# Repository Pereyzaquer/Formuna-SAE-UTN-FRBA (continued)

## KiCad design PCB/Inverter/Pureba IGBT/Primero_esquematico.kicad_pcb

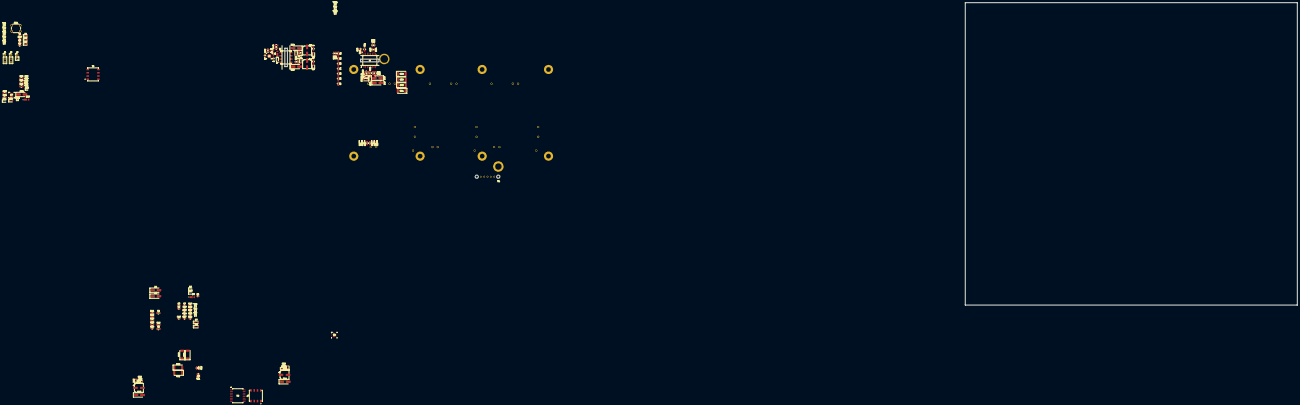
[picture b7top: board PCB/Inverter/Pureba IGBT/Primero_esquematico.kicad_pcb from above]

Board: 4 copper layers, 149 parts (1 on the bottom side), 78 nets.

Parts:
C1: 100pF; R_0603_1608Metric_Pad0.98x0.95mm_HandSolder
C2, C4, C17, C19, C32, C34, C35: 10uF; C_0805_2012Metric_Pad1.18x1.45mm_HandSolder
C3, C7, C13, C18, C22, C28: 100pF; C_0603_1608Metric_Pad1.08x0.95mm_HandSolder
C5, C20: 10pF; C_0603_1608Metric_Pad1.08x0.95mm_HandSolder
C6, C21: 47nF; C_0603_1608Metric_Pad1.08x0.95mm_HandSolder
C8, C9, C23, C24: 100nF; C_0603_1608Metric_Pad1.08x0.95mm_HandSolder
C10, C25: 220nF; C_0603_1608Metric_Pad1.08x0.95mm_HandSolder
C11, C12, C26, C27: 2.2uF; C_0805_2012Metric_Pad1.18x1.45mm_HandSolder
C14, C15, C29, C30: 22uF; CP_Elec_6.3x5.8
C16, C31: 1uF; C_0805_2012Metric_Pad1.18x1.45mm_HandSolder
C33: 47nF; R_0201_0603Metric_Pad0.64x0.40mm_HandSolder
D1, D2, D3, D15, D16, D28, D29, D34: APT2012EC; LED_0805_2012Metric_Pad1.15x1.40mm_HandSolder
D4, D5, D17, D18: STTH112A; D_SMA_Handsoldering
D6, D19: BAT54WS-7-F; D_SOD-323F
D7, D20: BZT52C2V7-TP; Nexperia_CFP3_SOD-123W
D8, D21: MMSZ5242B-7-F; Nexperia_CFP3_SOD-123W
D9, D22, D30: DFLZ24Q-7; DIO_DFLS130L-7
D10, D23, D31: 1N4148WS-Q; D_SOD-323F
D11, D12, D24, D25, D32: VS-10MQ100NTRPBF; D_SMA_Handsoldering
D13, D26: BZT52-B8V2_R1_00001; Nexperia_CFP3_SOD-123W
D14, D27: BZT52C18-7-F; Nexperia_CFP3_SOD-123W
D33: SZMM5Z5V6T1G; D_SOD-523
J1, J2: Molex 3; PinHeader_1x03_P2.54mm_Vertical
J3: Molex; PinHeader_1x02_P2.54mm_Vertical
R1, R28, R47: 6k8; R_0805_2012Metric_Pad1.20x1.40mm_HandSolder
R2, R3, R4, R5, R6, R7: 180k; R_0805_2012Metric_Pad1.20x1.40mm_HandSolder
R8, R9: 5k; R_0603_1608Metric_Pad0.98x0.95mm_HandSolder
R10: 15k; R_0603_1608Metric_Pad0.98x0.95mm_HandSolder
R11, R30: 590; R_0805_2012Metric_Pad1.20x1.40mm_HandSolder
R12, R31: 475; R_0805_2012Metric_Pad1.20x1.40mm_HandSolder
R13, R32: 307k; C_0603_1608Metric_Pad1.08x0.95mm_HandSolder
R14, R33: 37k; C_0603_1608Metric_Pad1.08x0.95mm_HandSolder
R15, R16, R34, R35: 2k; R_0805_2012Metric_Pad1.20x1.40mm_HandSolder
R17, R36: 12k1; C_0603_1608Metric_Pad1.08x0.95mm_HandSolder
R18, R37: 200k; C_0603_1608Metric_Pad1.08x0.95mm_HandSolder
R19, R20, R38, R39: 4.7; D_2512_6332Metric_Pad1.52x3.35mm_HandSolder
R21, R22, R40, R41: 10; D_2512_6332Metric_Pad1.52x3.35mm_HandSolder
R23, R42: 10; C_0603_1608Metric_Pad1.08x0.95mm_HandSolder
R24, R43: 154k; C_0603_1608Metric_Pad1.08x0.95mm_HandSolder
R25, R26, R44, R45: 100; C_0603_1608Metric_Pad1.08x0.95mm_HandSolder
R27, R46: 360; C_0603_1608Metric_Pad1.08x0.95mm_HandSolder
R29, R48: 15k; R_0805_2012Metric_Pad1.20x1.40mm_HandSolder
R49: 307k; R_0201_0603Metric_Pad0.64x0.40mm_HandSolder
R50: 37k; R_0201_0603Metric_Pad0.64x0.40mm_HandSolder
R51: 12k; R_0201_0603Metric_Pad0.64x0.40mm_HandSolder
R52: 73k2; R_0201_0603Metric_Pad0.64x0.40mm_HandSolder
R53: 110k; R_0805_2012Metric_Pad1.20x1.40mm_HandSolder
R54: 1k5; R_0805_2012Metric_Pad1.20x1.40mm_HandSolder
SW1: SW_Push; SW_PUSH_6mm
T1, T2: 750317595; WE-FLYTI_EP7_4436
T3: 750317605; WE-FLYTI_EP7_4436
TP1, TP2, TP3, TP4, TP5: TP; TestPoint_Pad_1.0x1.0mm
TP6, TP7, TP8, TP9, TP10, TP11, TP12: TestPoint; TestPoint_Pad_1.0x1.0mm
U1: HAH3DR 800-S07SP4
U2: FS950R08A6P2BBPSA1; IC_FS950R08A6P2BBPSA1
U3, U5, U7: LM25180QNGURQ1; NGU0008C
U4, U6: UCC21750QDWRQ1; SOIC16_DW_TEX-M

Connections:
+3.3V: C16.2, C31.2, C34.2, C35.2, D32.1 (K), D33.1 (K), R8.1, R9.1, R10.2, R54.1, TP12.1, U4.15 (VCC), U6.15 (VCC)
+15V: C2.2, C4.2, C17.2, C19.2, C32.2, D9.2 (A), D22.2 (A), D30.2 (A), J3.1, R13.1, R32.1, R49.1, T1.4, T2.4, T3.4, U3.3 (VIN), U5.3 (VIN), U7.3 (VIN)
/Gate_Driver/*FLT: D1.2 (A), R8.2, U4.13 (*FLT), U6.13 (*FLT)
/Gate_Driver/C1_In_neg: C7.2, C28.2, J1.2, R25.1, R45.2, TP1.1
/Gate_Driver/C1_In_pos: C13.2, C22.2, J1.3, R26.2, R44.1, TP2.1
/Gate_Driver/Colec_2: D17.1 (K), R7.2, U2.C2
/Gate_Driver/G1: R19.1, R20.1, R21.1, R22.2, U2.G1, U4.7 (CLMPI)
/Gate_Driver/G2: R38.1, R39.1, R40.1, R41.2, U2.G2, U6.7 (CLMPI)
/Gate_Driver/GDsupply5/+15V: C24.2, C27.2, C30.1, D24.1 (K), D27.1 (K), R48.1, TP11.1, U6.5 (VDD)
/Gate_Driver/GDsupply5/-8V: C23.1, C26.1, C29.2, D25.2 (A), D26.2 (A), D28.1 (K), TP9.1, U6.8 (VEE)
/Gate_Driver/GDsupply5/DESAT: C18.2, D19.1 (K), D21.1 (K), R30.2, R31.1, U6.2 (DESAT)
/Gate_Driver/GDsupply5/S_HV: C20.1, R1.2, R2.1, R42.1
/Gate_Driver/GDsupply/+15V: C9.2, C12.2, C15.1, D11.1 (K), D14.1 (K), R29.1, TP8.1, U4.5 (VDD)
/Gate_Driver/GDsupply/-8V: C8.1, C11.1, C14.2, D12.2 (A), D13.2 (A), D15.1 (K), TP6.1, U4.8 (VEE)
/Gate_Driver/GDsupply/DESAT: C3.2, D6.1 (K), D8.1 (K), R11.2, R12.1, U4.2 (DESAT)
/Gate_Driver/ISO_GND: C3.1, C5.2, C8.2, C9.1, C11.2, C12.1, C14.1, C15.2, D6.2 (A), D8.2 (A), D13.1 (K), D14.2 (A), D16.1 (K), R11.1, R28.1, T1.6, T1.7, TP7.1, U2.T1, U4.3 (COM)
/Gate_Driver/ISO_GND_2: C18.1, C20.2, C23.2, C24.1, C26.2, C27.1, C29.1, C30.2, D19.2 (A), D21.2 (A), D26.1 (K), D27.2 (A), D29.1 (K), R1.1, R30.1, R47.1, T2.6, T2.7, TP10.1, U6.3 (COM)
/Gate_Driver/RDY: D2.2 (A), R9.2, U4.12 (RDY), U6.12 (RDY)
/Gate_Driver/Reset: C1.2, D3.2 (A), R10.1, SW1.2, U4.14 (RST/EN), U6.14 (RST/EN)
/Gate_Driver/S_TEMP: C5.1, R23.1, U2.T2
/Gate_Driver/Temp1: C10.1, J2.2, R27.1, TP3.1
/Gate_Driver/VCC_DC: D4.1 (K), U2.C1
/Gate_Driver/V_MP1: C25.1, J2.3, R46.1, TP4.1
GND: C1.1, C2.1, C4.1, C6.1, C7.1, C10.2, C13.1, C16.1, C17.1, C19.1, C21.1, C22.1, C25.2, C28.1, C31.1, C32.1, C33.1, C34.1, C35.1, D1.1 (K), D2.1 (K), D3.1 (K), D33.2 (A), D34.1 (K), J1.1, J2.1, J3.2, R14.2, R17.2, R33.2, R36.2, R50.2, R51.2, SW1.1, T3.5, T3.6, TP5.1, U3.8 (GND), U3.9 (PAD), U4.9 (GND), U5.8 (GND), U5.9 (PAD), U6.9 (GND), U7.8 (GND), U7.9 (PAD)
unnamed: D4.2 (A), D5.1 (K)
unnamed: D5.2 (A), D7.2 (A), R15.1, R16.1
unnamed: D7.1 (K), R12.2
unnamed: D10.2 (A), R24.1, T1.1, U3.1 (SW)
unnamed: D9.1 (K), D10.1 (K)
unnamed: D11.2 (A), T1.5
unnamed: D12.1 (K), T1.8
unnamed: D15.2 (A), R28.2
unnamed: D16.2 (A), R29.2
unnamed: D17.2 (A), D18.1 (K)
unnamed: D18.2 (A), D20.2 (A), R34.1, R35.1
unnamed: D20.1 (K), R31.2
unnamed: D22.1 (K), D23.1 (K)
unnamed: D23.2 (A), R43.1, T2.1, U5.1 (SW)
unnamed: D24.2 (A), T2.5
unnamed: D25.1 (K), T2.8
unnamed: D28.2 (A), R47.2
unnamed: D29.2 (A), R48.2
unnamed: D30.1 (K), D31.1 (K)
unnamed: D31.2 (A), R53.1, T3.1, U7.1 (SW)
unnamed: D32.2 (A), T3.7, T3.8
unnamed: D34.2 (A), R54.2
unnamed: R2.2, R3.1
unnamed: R3.2, R4.1
unnamed: R4.2, R5.1
unnamed: R5.2, R6.1
unnamed: R6.2, R7.1
unnamed: R13.2, R14.1, U3.4 (EN_UVLO)
unnamed: R24.2, U3.2 (FB)
unnamed: R18.2, U3.7 (RSET)
unnamed: C6.2, U3.5 (SS_BIAS)
unnamed: R17.1, R18.1, U3.6 (TC)
unnamed: R23.2, U4.1 (AIN)
unnamed: R27.2, U4.16 (APWM)
unnamed: R26.1, U4.11 (IN)
unnamed: R25.2, U4.10 (IN+)
unnamed: R15.2, R16.2, R19.2, R20.2, U4.4 (OUTH)
unnamed: R21.2, R22.1, U4.6 (OUTL)
unnamed: R32.2, R33.1, U5.4 (EN_UVLO)
unnamed: R43.2, U5.2 (FB)
unnamed: R37.2, U5.7 (RSET)
unnamed: C21.2, U5.5 (SS_BIAS)
unnamed: R36.1, R37.1, U5.6 (TC)
unnamed: R42.2, U6.1 (AIN)
unnamed: R46.2, U6.16 (APWM)
unnamed: R45.1, U6.11 (IN)
unnamed: R44.2, U6.10 (IN+)
unnamed: R34.2, R35.2, R38.2, R39.2, U6.4 (OUTH)
unnamed: R40.2, R41.1, U6.6 (OUTL)
unnamed: R49.2, R50.1, U7.4 (EN_UVLO)
unnamed: R53.2, U7.2 (FB)
unnamed: R52.2, U7.7 (RSET)
unnamed: C33.2, U7.5 (SS_BIAS)
unnamed: R51.1, R52.1, U7.6 (TC)

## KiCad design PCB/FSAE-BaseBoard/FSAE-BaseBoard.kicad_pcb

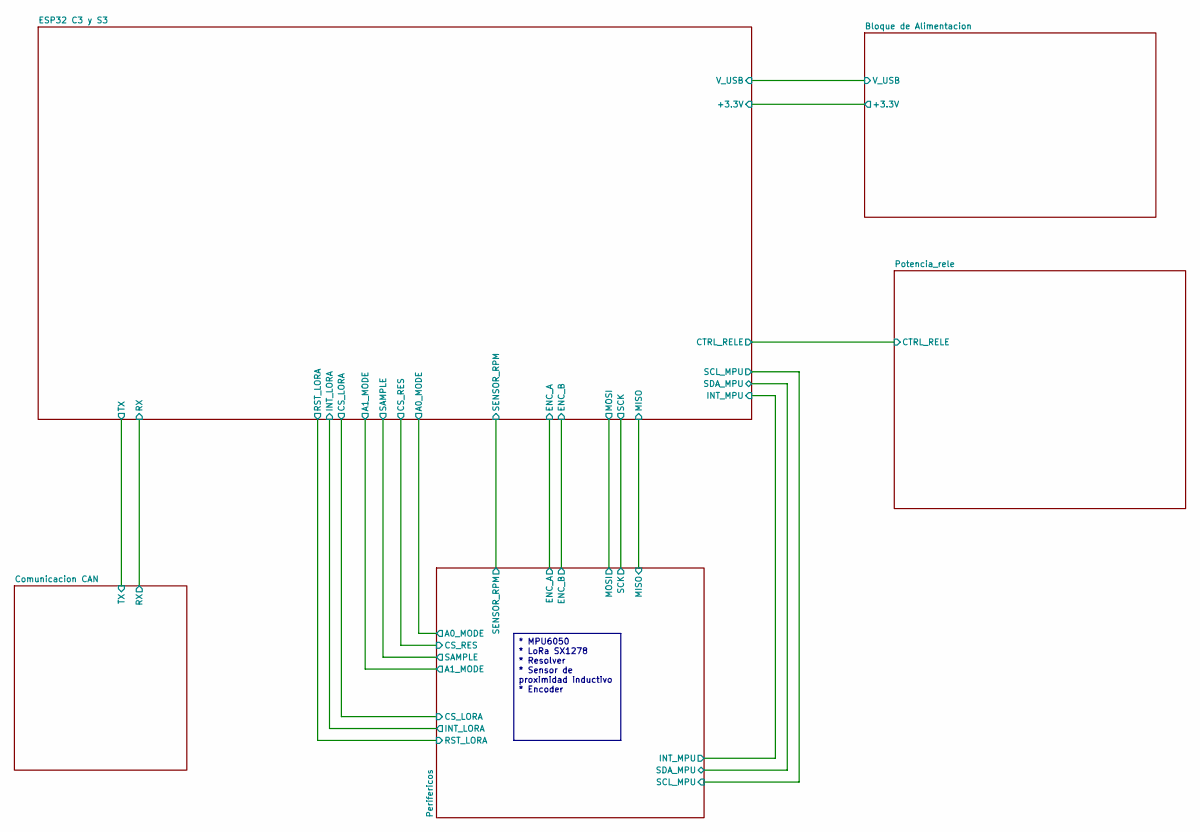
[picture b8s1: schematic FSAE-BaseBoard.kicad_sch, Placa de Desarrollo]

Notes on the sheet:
* MPU6050 * LoRa SX1278 * Resolver * Sensor de proximidad inductivo * Encoder

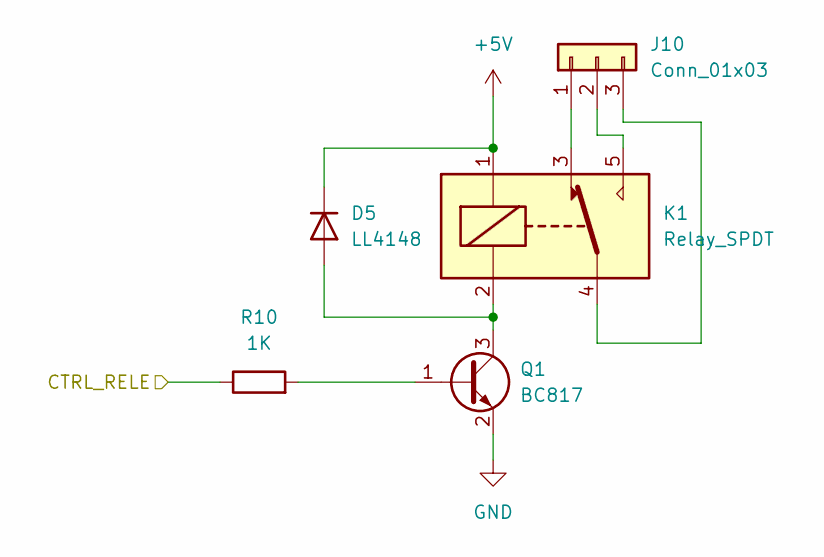
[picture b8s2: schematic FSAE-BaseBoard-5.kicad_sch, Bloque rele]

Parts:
D5: LL4148; D_MiniMELF
J10: Conn_01x03; PinHeader_1x03_P2.54mm_Vertical
K1: Relay_SPDT; Relay_SPDT_Omron-G5LE-1
Q1: BC817; SOT-23
R10: 1K; R_0805_2012Metric_Pad1.20x1.40mm_HandSolder

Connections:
+5V: D5.1 (K), K1.1; also elsewhere on the board
/ESP32 C3 y S3/CTRL_RELE: R10.1; also elsewhere on the board
GND: Q1.2 (E); also elsewhere on the board
unnamed: D5.2 (A), K1.2, Q1.3 (C)
unnamed: J10.1, K1.3
unnamed: J10.2, K1.5
unnamed: J10.3, K1.4
unnamed: Q1.1 (B), R10.2

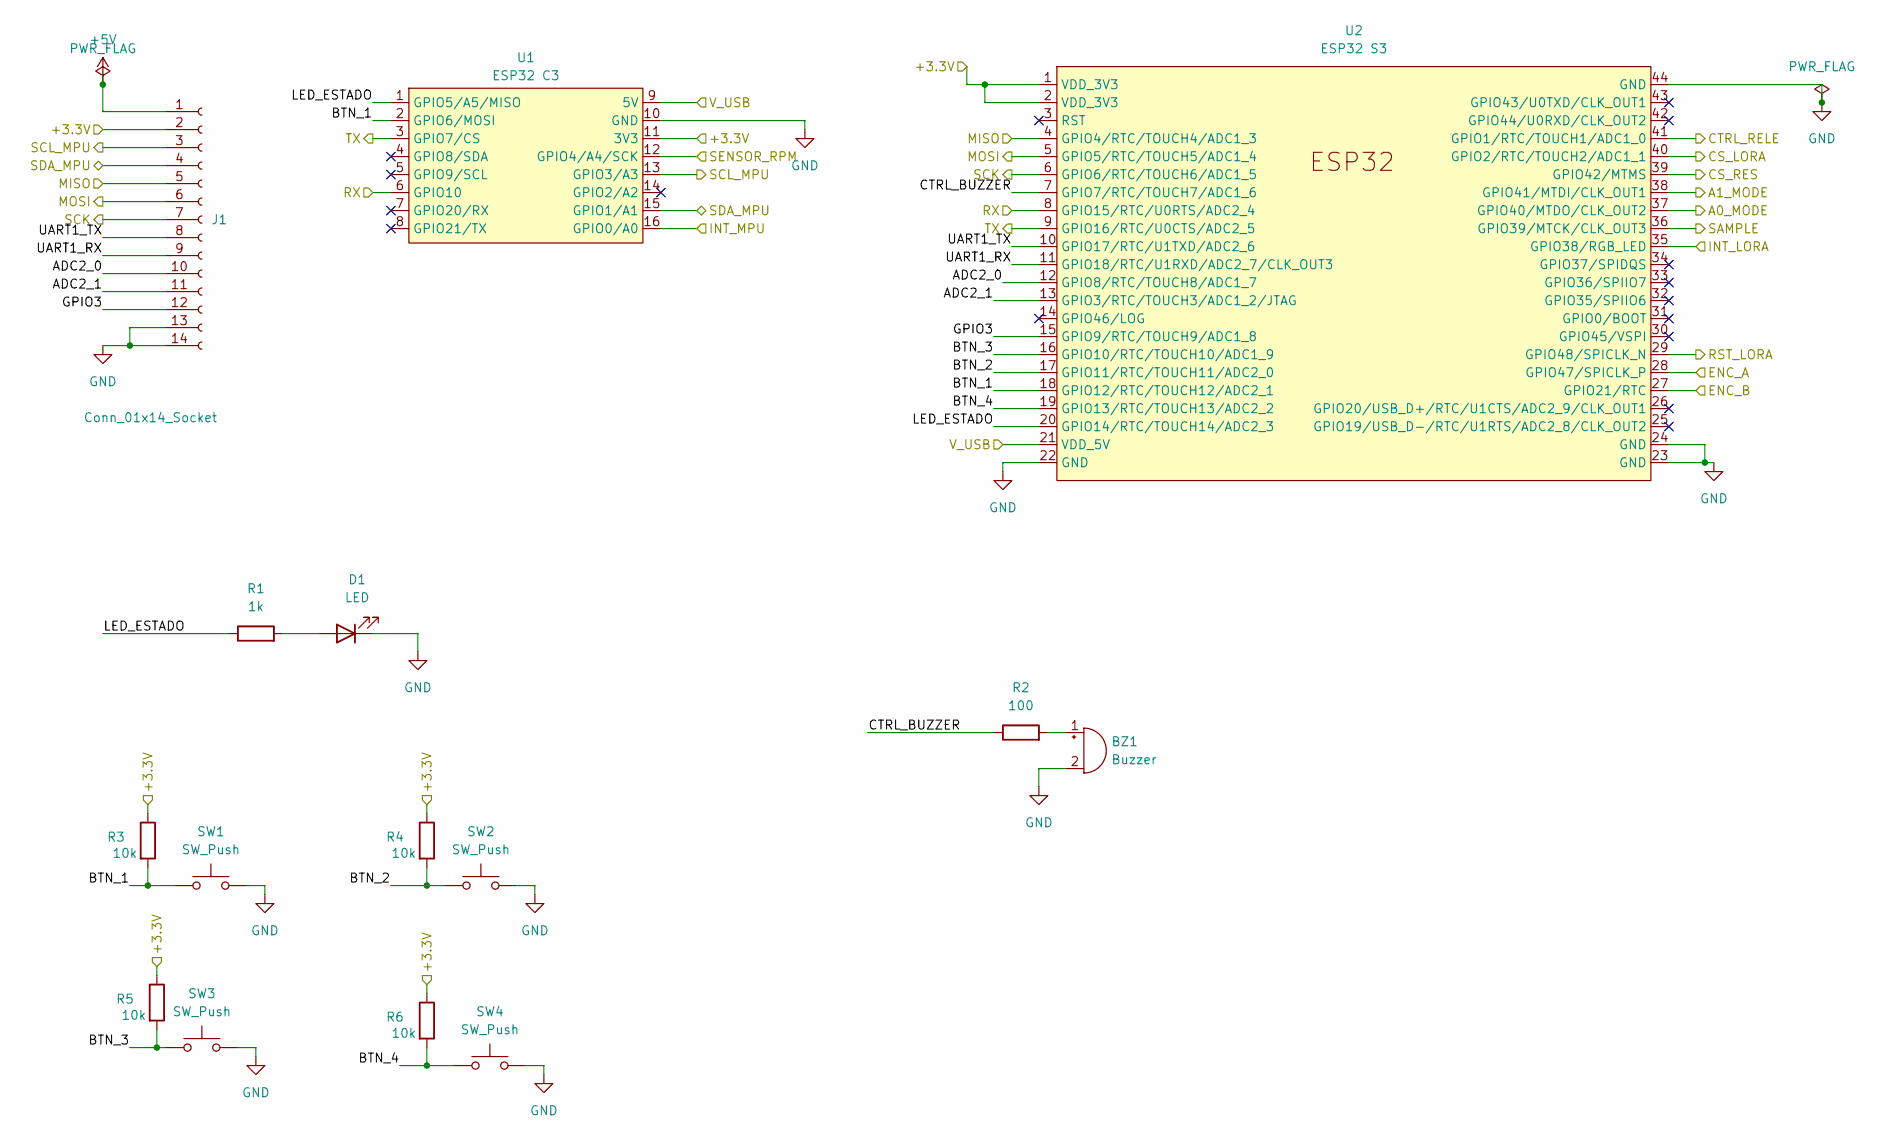
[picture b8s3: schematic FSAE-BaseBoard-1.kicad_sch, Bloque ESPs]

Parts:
BZ1: Buzzer; Buzzer_12x9.5RM7.6
D1: LED; LED_0805_2012Metric_Pad1.15x1.40mm_HandSolder
J1: Conn_01x14_Socket; PinSocket_1x14_P2.54mm_Vertical
R1: 1k; R_0805_2012Metric_Pad1.20x1.40mm_HandSolder
R2: 100; R_0805_2012Metric_Pad1.20x1.40mm_HandSolder
R3, R4, R5, R6: 10k; R_0805_2012Metric_Pad1.20x1.40mm_HandSolder
SW1, SW2, SW3, SW4: SW_Push; SW_PUSH_6mm_H5mm
U1: ESP32 C3; ESP32 C3 SM
U2: ESP32 S3

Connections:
+3.3V: J1.2, R3.1, R4.1, R5.1, R6.1, U1.11 (3V3), U2.1 (VDD_3V3), U2.2 (VDD_3V3); also elsewhere on the board
+5V: J1.1; also elsewhere on the board
/Bloque de Alimentacion/V_USB: U1.9 (5V), U2.21 (VDD_5V); also elsewhere on the board
/Comunicacion CAN/RX: U1.6 (GPIO10), U2.8 (GPIO15/RTC/U0RTS/ADC2_4); also elsewhere on the board
/Comunicacion CAN/TX: U1.3 (GPIO7/CS), U2.9 (GPIO16/RTC/U0CTS/ADC2_5); also elsewhere on the board
/ESP32 C3 y S3/A0_MODE: U2.37 (GPIO40/MTDO/CLK_OUT2); also elsewhere on the board
/ESP32 C3 y S3/A1_MODE: U2.38 (GPIO41/MTDI/CLK_OUT1); also elsewhere on the board
/ESP32 C3 y S3/ADC2_0: J1.10, U2.12 (GPIO8/RTC/TOUCH8/ADC1_7)
/ESP32 C3 y S3/ADC2_1: J1.11, U2.13 (GPIO3/RTC/TOUCH3/ADC1_2/JTAG)
/ESP32 C3 y S3/BTN_1: R3.2, SW1.1, U1.2 (GPIO6/MOSI), U2.18 (GPIO12/RTC/TOUCH12/ADC2_1)
/ESP32 C3 y S3/BTN_2: R4.2, SW2.1, U2.17 (GPIO11/RTC/TOUCH11/ADC2_0)
/ESP32 C3 y S3/BTN_3: R5.2, SW3.1, U2.16 (GPIO10/RTC/TOUCH10/ADC1_9)
/ESP32 C3 y S3/BTN_4: R6.2, SW4.1, U2.19 (GPIO13/RTC/TOUCH13/ADC2_2)
/ESP32 C3 y S3/CS_LORA: U2.40 (GPIO2/RTC/TOUCH2/ADC1_1); also elsewhere on the board
/ESP32 C3 y S3/CS_RES: U2.39 (GPIO42/MTMS); also elsewhere on the board
/ESP32 C3 y S3/CTRL_BUZZER: R2.1, U2.7 (GPIO7/RTC/TOUCH7/ADC1_6)
/ESP32 C3 y S3/CTRL_RELE: U2.41 (GPIO1/RTC/TOUCH1/ADC1_0); also elsewhere on the board
/ESP32 C3 y S3/ENC_A: U2.28 (GPIO47/SPICLK_P); also elsewhere on the board
/ESP32 C3 y S3/ENC_B: U2.27 (GPIO21/RTC); also elsewhere on the board
/ESP32 C3 y S3/GPIO3: J1.12, U2.15 (GPIO9/RTC/TOUCH9/ADC1_8)
/ESP32 C3 y S3/INT_LORA: U2.35 (GPIO38/RGB_LED); also elsewhere on the board
/ESP32 C3 y S3/INT_MPU: U1.16 (GPIO0/A0); also elsewhere on the board
/ESP32 C3 y S3/LED_ESTADO: R1.1, U1.1 (GPIO5/A5/MISO), U2.20 (GPIO14/RTC/TOUCH14/ADC2_3)
/ESP32 C3 y S3/MISO: J1.5, U2.4 (GPIO4/RTC/TOUCH4/ADC1_3); also elsewhere on the board
/ESP32 C3 y S3/MOSI: J1.6, U2.5 (GPIO5/RTC/TOUCH5/ADC1_4); also elsewhere on the board
/ESP32 C3 y S3/RST_LORA: U2.29 (GPIO48/SPICLK_N); also elsewhere on the board
/ESP32 C3 y S3/SAMPLE: U2.36 (GPIO39/MTCK/CLK_OUT3); also elsewhere on the board
/ESP32 C3 y S3/SCK: J1.7, U2.6 (GPIO6/RTC/TOUCH6/ADC1_5); also elsewhere on the board
/ESP32 C3 y S3/SCL_MPU: J1.3, U1.13 (GPIO3/A3); also elsewhere on the board
/ESP32 C3 y S3/SDA_MPU: J1.4, U1.15 (GPIO1/A1); also elsewhere on the board
/ESP32 C3 y S3/SENSOR_RPM: U1.12 (GPIO4/A4/SCK); also elsewhere on the board
/ESP32 C3 y S3/UART1_RX: J1.9, U2.11 (GPIO18/RTC/U1RXD/ADC2_7/CLK_OUT3)
/ESP32 C3 y S3/UART1_TX: J1.8, U2.10 (GPIO17/RTC/U1TXD/ADC2_6)
GND: BZ1.2 (-), D1.1 (K), J1.13, J1.14, SW1.2, SW2.2, SW3.2, SW4.2, U1.10 (GND), U2.22 (GND), U2.23 (GND), U2.24 (GND), U2.44 (GND); also elsewhere on the board
unnamed: BZ1.1 (+), R2.2
unnamed: D1.2 (A), R1.2

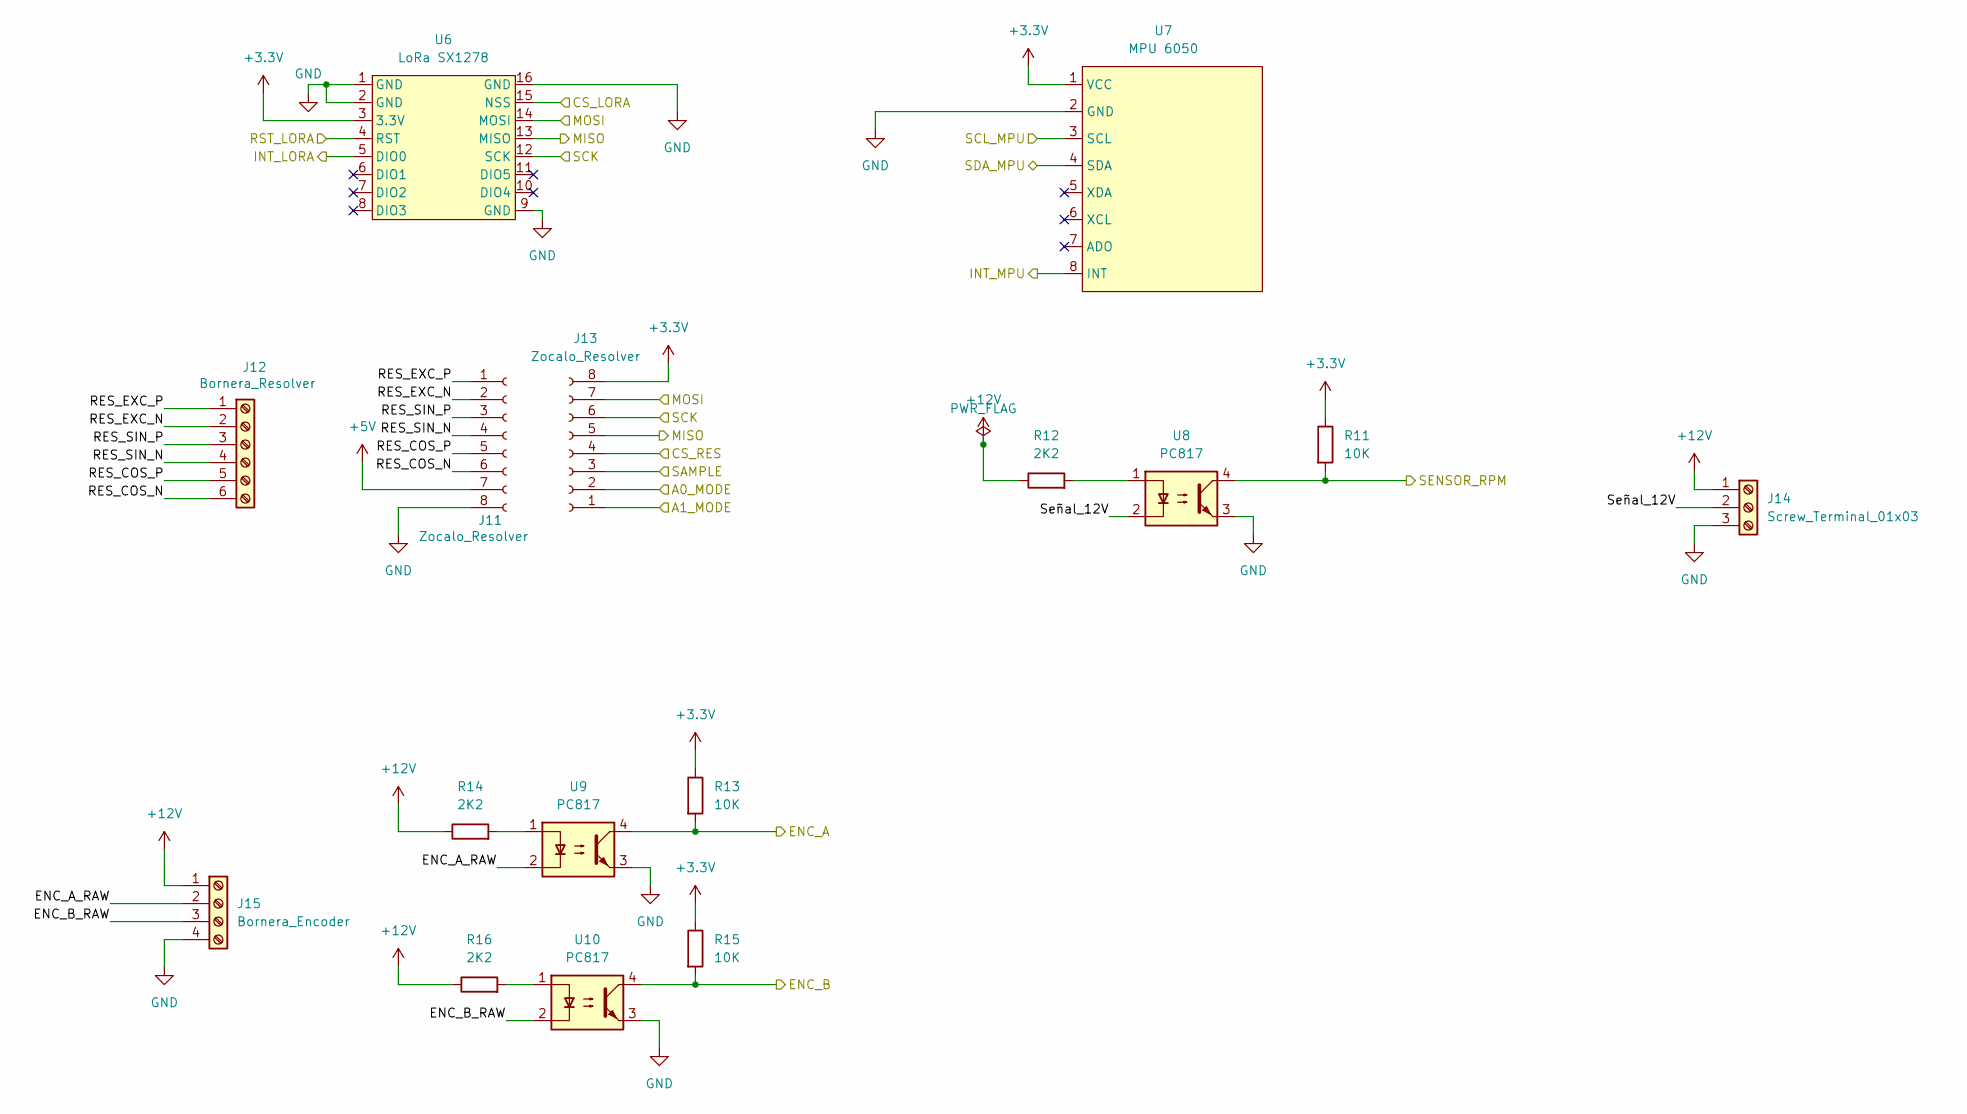
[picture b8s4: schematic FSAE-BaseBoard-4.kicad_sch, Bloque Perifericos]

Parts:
J11, J13: Zocalo_Resolver; PinSocket_1x08_P2.54mm_Vertical
J12: Bornera_Resolver; TerminalBlock_Phoenix_PT-1,5-6-3.5-H_1x06_P3.50mm_Horizontal
J14: Screw_Terminal_01x03; TerminalBlock_Phoenix_PT-1,5-3-3.5-H_1x03_P3.50mm_Horizontal
J15: Bornera_Encoder; TerminalBlock_Phoenix_PT-1,5-4-3.5-H_1x04_P3.50mm_Horizontal
R11, R13, R15: 10K; R_0805_2012Metric_Pad1.20x1.40mm_HandSolder
R12, R14, R16: 2K2; R_0805_2012Metric_Pad1.20x1.40mm_HandSolder
U6: LoRa SX1278; LoRa_SX178
U7: MPU 6050; MPU6050
U8, U9, U10: PC817; DIP-4_W7.62mm

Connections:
+3.3V: J13.8, R11.1, R13.1, R15.1, U6.3 (3.3V), U7.1 (VCC); also elsewhere on the board
+5V: J11.7; also elsewhere on the board
+12V: J14.1, J15.1, R12.1, R14.1, R16.1
/ESP32 C3 y S3/A0_MODE: J13.2; also elsewhere on the board
/ESP32 C3 y S3/A1_MODE: J13.1; also elsewhere on the board
/ESP32 C3 y S3/CS_LORA: U6.15 (NSS); also elsewhere on the board
/ESP32 C3 y S3/CS_RES: J13.4; also elsewhere on the board
/ESP32 C3 y S3/ENC_A: R13.2, U9.4; also elsewhere on the board
/ESP32 C3 y S3/ENC_B: R15.2, U10.4; also elsewhere on the board
/ESP32 C3 y S3/INT_LORA: U6.5 (DIO0); also elsewhere on the board
/ESP32 C3 y S3/INT_MPU: U7.8 (INT); also elsewhere on the board
/ESP32 C3 y S3/MISO: J13.5, U6.13 (MISO); also elsewhere on the board
/ESP32 C3 y S3/MOSI: J13.7, U6.14 (MOSI); also elsewhere on the board
/ESP32 C3 y S3/RST_LORA: U6.4 (RST); also elsewhere on the board
/ESP32 C3 y S3/SAMPLE: J13.3; also elsewhere on the board
/ESP32 C3 y S3/SCK: J13.6, U6.12 (SCK); also elsewhere on the board
/ESP32 C3 y S3/SCL_MPU: U7.3 (SCL); also elsewhere on the board
/ESP32 C3 y S3/SDA_MPU: U7.4 (SDA); also elsewhere on the board
/ESP32 C3 y S3/SENSOR_RPM: R11.2, U8.4; also elsewhere on the board
/Perifericos/ENC_A_RAW: J15.2, U9.2
/Perifericos/ENC_B_RAW: J15.3, U10.2
/Perifericos/RES_COS_N: J11.6, J12.6
/Perifericos/RES_COS_P: J11.5, J12.5
/Perifericos/RES_EXC_N: J11.2, J12.2
/Perifericos/RES_EXC_P: J11.1, J12.1
/Perifericos/RES_SIN_N: J11.4, J12.4
/Perifericos/RES_SIN_P: J11.3, J12.3
/Perifericos/Señal_12V: J14.2, U8.2
GND: J11.8, J14.3, J15.4, U6.1 (GND), U6.2 (GND), U6.9 (GND), U6.16 (GND), U7.2 (GND), U8.3, U9.3, U10.3; also elsewhere on the board
unnamed: R12.2, U8.1
unnamed: R14.2, U9.1
unnamed: R16.2, U10.1

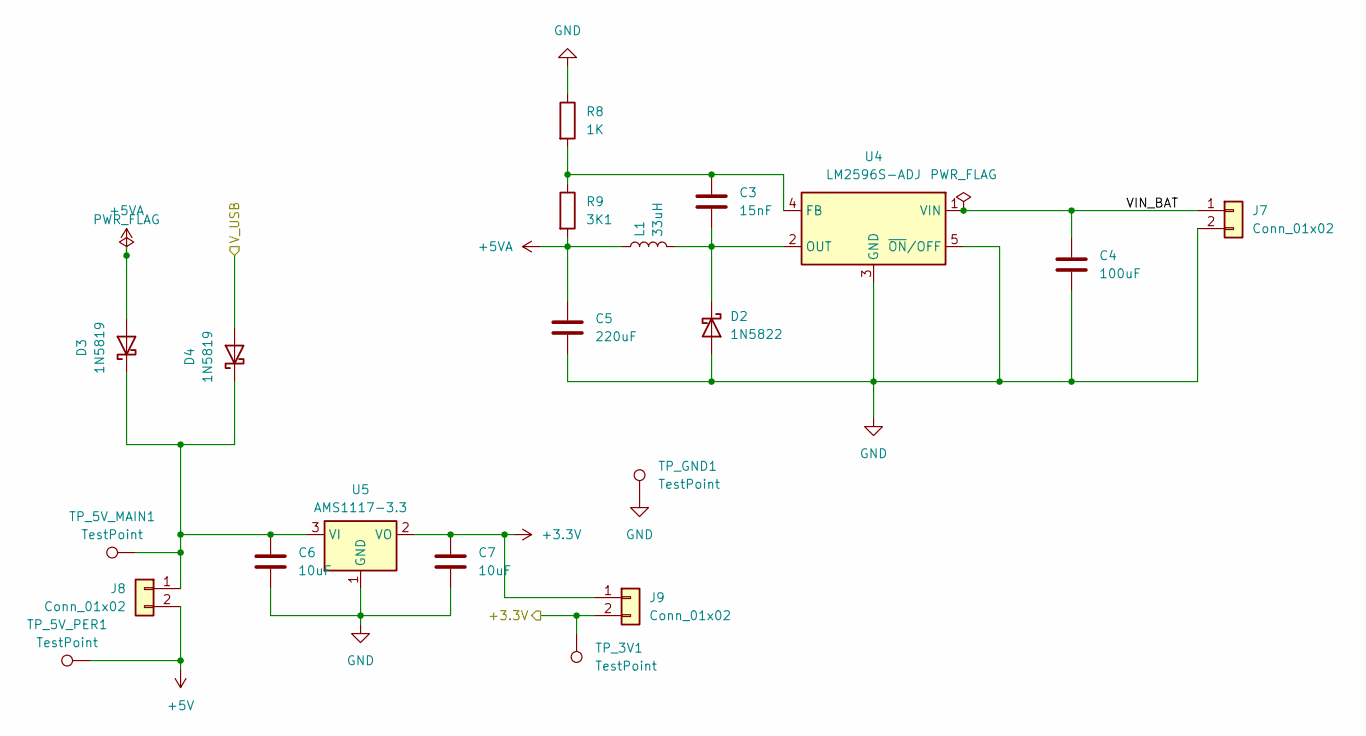
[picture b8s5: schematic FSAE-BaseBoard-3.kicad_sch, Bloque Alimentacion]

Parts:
C3: 15nF; C_0805_2012Metric_Pad1.18x1.45mm_HandSolder
C4: 100uF; C_Radial_D6.3mm_H11.0mm_P2.50mm
C5: 220uF; C_Radial_D6.3mm_H11.0mm_P2.50mm
C6, C7: 10uF; C_0805_2012Metric_Pad1.18x1.45mm_HandSolder
D2: 1N5822; D_DO-201AD_P15.24mm_Horizontal
D3, D4: 1N5819; D_DO-41_SOD81_P10.16mm_Horizontal
J7, J8, J9: Conn_01x02; PinHeader_1x02_P2.54mm_Vertical
L1: 33uH; L_Wuerth_WE-PD-Typ-LS_Handsoldering
R8: 1K; R_0805_2012Metric_Pad1.20x1.40mm_HandSolder
R9: 3K1; R_0805_2012Metric_Pad1.20x1.40mm_HandSolder
TP_3V1, TP_5V_MAIN1, TP_5V_PER1: TestPoint; TestPoint_THTPad_D2.0mm_Drill1.0mm
TP_GND1: TestPoint; TestPoint_THTPad_2.0x2.0mm_Drill1.0mm
U4: LM2596S-ADJ; TO-263-5_TabPin3
U5: AMS1117-3.3; SOT-223-3_TabPin2

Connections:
+3.3V: C7.1, J9.1, J9.2, TP_3V1.1 (1_1), U5.2 (VO); also elsewhere on the board
+5V: J8.2, TP_5V_PER1.1 (1_1); also elsewhere on the board
+5VA: C5.1, D3.2 (A), L1.1, R9.2
/Bloque de Alimentacion/VIN_BAT: C4.1, J7.1, U4.1 (VIN)
/Bloque de Alimentacion/V_USB: D4.2 (A); also elsewhere on the board
GND: C4.2, C5.2, C6.2, C7.2, D2.2 (A), J7.2, R8.1, TP_GND1.1 (1_1), U4.3 (GND), U4.5 (~ON/OFF), U5.1 (GND); also elsewhere on the board
unnamed: C3.2, D2.1 (K), L1.2, U4.2 (OUT)
unnamed: C6.1, D3.1 (K), D4.1 (K), J8.1, TP_5V_MAIN1.1 (1_1), U5.3 (VI)
unnamed: C3.1, R8.2, R9.1, U4.4 (FB)

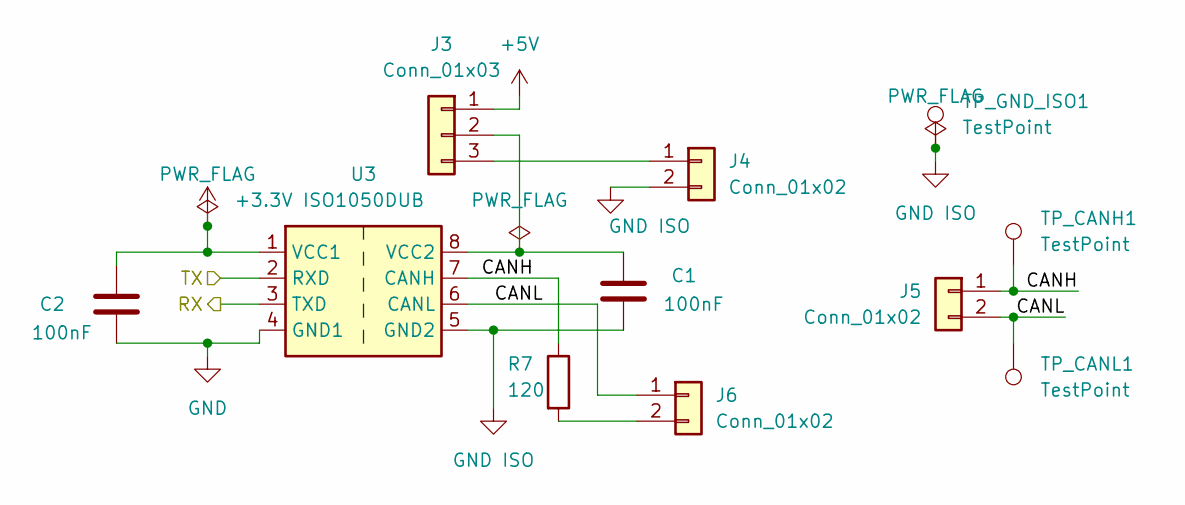
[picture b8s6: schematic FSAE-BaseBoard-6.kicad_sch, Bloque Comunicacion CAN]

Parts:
C1, C2: 100nF; C_0805_2012Metric_Pad1.18x1.45mm_HandSolder
J3: Conn_01x03; PinHeader_1x03_P2.54mm_Vertical
J4, J5, J6: Conn_01x02; PinHeader_1x02_P2.54mm_Vertical
R7: 120; R_0805_2012Metric_Pad1.20x1.40mm_HandSolder
TP_CANH1: TestPoint; TestPoint_THTPad_D2.0mm_Drill1.0mm
TP_CANL1: TestPoint; TestPoint_THTPad_D2.0mm_Drill1.0mm
TP_GND_ISO1: TestPoint; TestPoint_THTPad_2.0x2.0mm_Drill1.0mm
U3: ISO1050DUB; SOP-8_6.62x9.15mm_P2.54mm

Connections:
+3.3V: C2.1, U3.1 (VCC1); also elsewhere on the board
+5V: J3.1; also elsewhere on the board
/Comunicacion CAN/CANH: J5.1, R7.1, TP_CANH1.1 (1_1), U3.7 (CANH)
/Comunicacion CAN/CANL: J5.2, J6.1, TP_CANL1.1 (1_1), U3.6 (CANL)
/Comunicacion CAN/RX: U3.3 (TXD); also elsewhere on the board
/Comunicacion CAN/TX: U3.2 (RXD); also elsewhere on the board
GND: C2.2, U3.4 (GND1); also elsewhere on the board
GND ISO: C1.2, J4.2, TP_GND_ISO1.1 (1_1), U3.5 (GND2)
unnamed: C1.1, J3.2, U3.8 (VCC2)
unnamed: J3.3, J4.1
unnamed: J6.2, R7.2

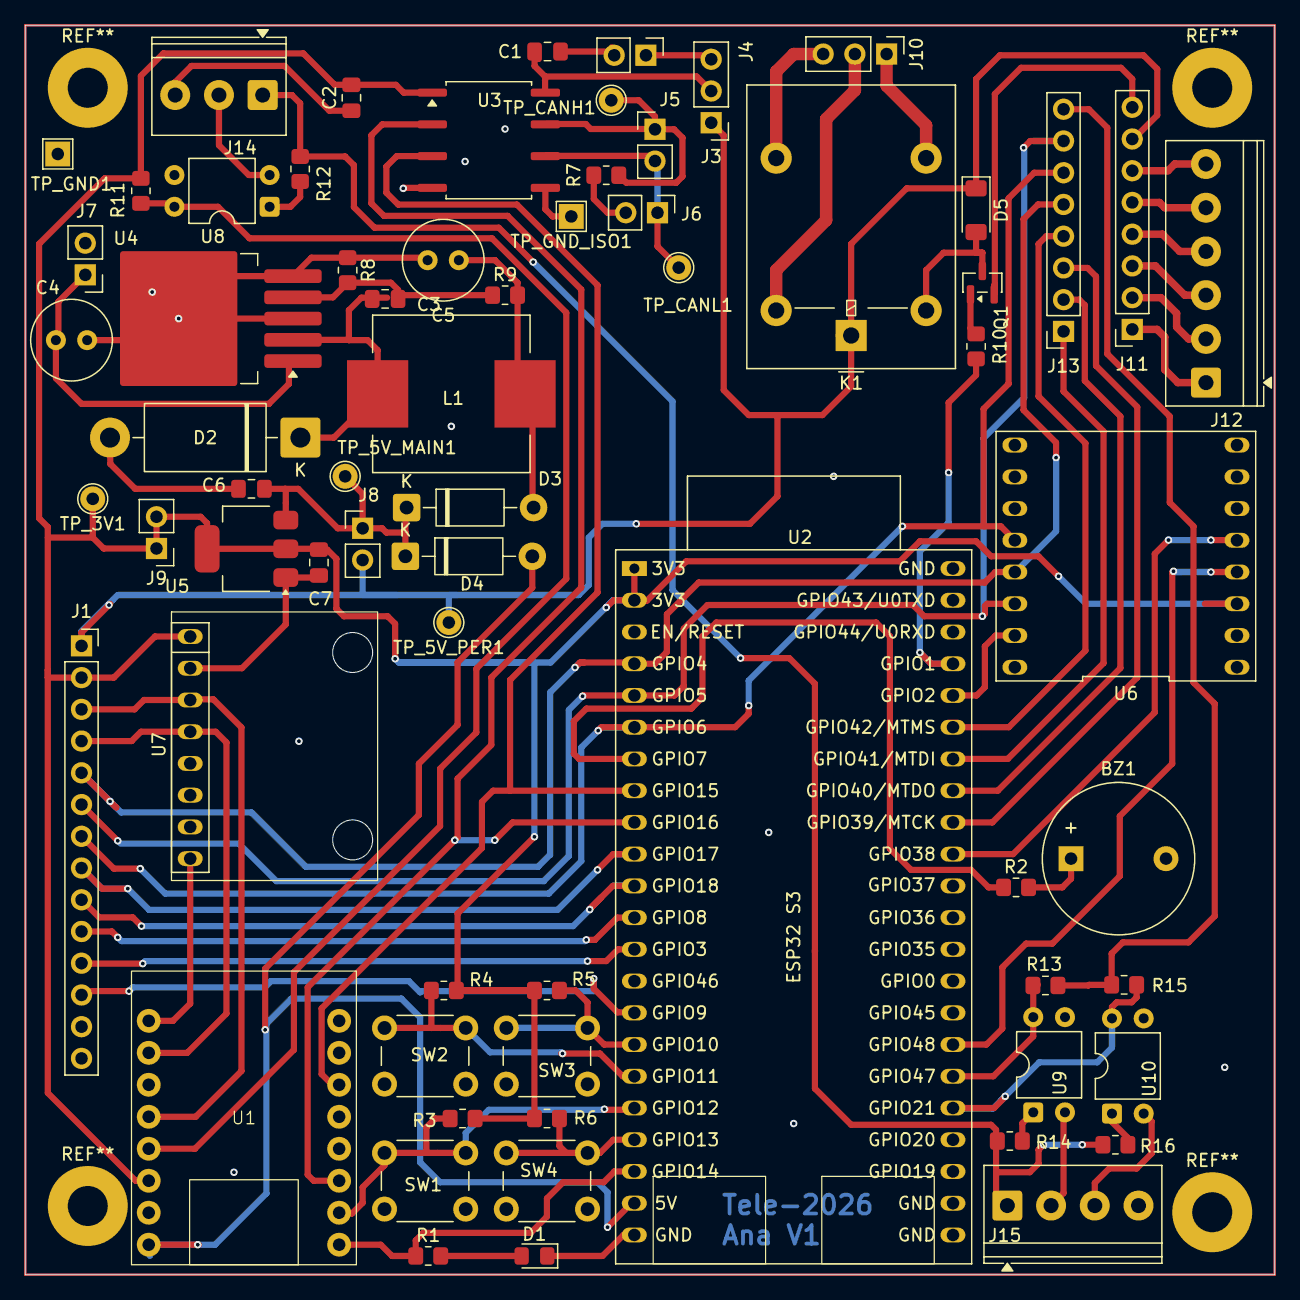
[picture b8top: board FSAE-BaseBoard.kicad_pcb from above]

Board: 2 copper layers, 100.0 x 100.0 mm, 67 parts (0 on the bottom side), 65 nets.

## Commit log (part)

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2025-10-20 Add guidelines for repository organization
2025-10-23 Add project information to ReadMe.dm
2025-10-23 Rename ReadMe.dm to ReadMe.md
2025-10-23 Fix formatting of project information header
2025-10-23 Update contact information in README
2025-10-23 Add PDF link to README
    Added a link to the PDF document in the README.
2025-12-23 Primer commit incluyendo el pdf y codigo del primer concepto de maquina de estados de la ECU
2025-12-24 Cargo el codigo inicial para comenzar a programar con algunos comentario y emprolijado
2025-12-24 Agregado de comentarios
2025-12-26 Se carga la simulacion en LTSpice del sistema APPS con potenciometros y distintas funciones transferencias y sin cruces entre ambas
2025-12-29 Se agrega proyecto basico para ESP32 C3 super mini, para los sensores de RPM de las ruedas
2025-12-31 cosas
2026-01-04 Actualizacion de archivos de simulacion
2026-01-08 Emprolije un poco los archivos y acomode un poco el setup del OTA para poder copiar y pegar el cpp y los includes de los .h en los proximos proyectos
2026-01-08 Agrego una version con el esp32 C3 super mini funcionando con el modulo can haciendo un loopback (no comunica por can solo es una prueba con el integrado del modulo can) y comunicacion por telnet ya 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
2026-01-09 Subo el codigo del ESP32 C3 super mini ya funcionando con el modulo CAN y habiendo comunicado con un arduino nano.
2026-01-17 Agrego la libreria de kicad arreglada con dos proyectos, uno de la ECU y otro del sensor RPM (este ultimo terminado)
2026-02-02 Modificacion de la placa pcb del modelo de comunicacion CAN por uno aisaldo y con fuente buck para el ESP32 C3
2026-02-05 Implementacion del sensor RPM
2026-02-19 Creacion de la placa de desarrollo y actualizalcion del esquematico
2026-02-19 Eliminar carpeta
2026-03-08 Actualizacion de la placa de desarollo - v.2
2026-04-12 Actualizacion diseño BaseBoard
2026-04-14 Reduccion de vias
2026-04-16 ModificacionesByNico
    Corregi una eleccion de footprint y arregle un poco el layout tambien detecte una falla que no solucione que es el echo que los smd y lo th van a tener problemas para soldarlos
2026-05-08 Agrega archivos iniciales para BaseBoard v2
2026-05-09 Cosas Basicas
    Primera pcb con el inverter, diseño descartado por falta de espacio
2026-05-11 Correcciones incompletas e instalaciones de un par de extensiones copadas
2026-05-11 paso mierda q tenia a esta rama
2026-05-12 Termine el circuito de corriente
2026-05-12 Actualizacion BaseBoard v2
2026-05-15 Coloque filtros y sensores
2026-05-21 Agrego esquematico avanzado del circuito de precarga
2026-06-13 Esquematico practicamente terminado
2026-06-19 Un par de cosas q corregi del ERC pero sigue mal
2026-06-20 Esquematico Listo
2026-06-21 Un par de cosas mas
2026-06-22 Sigo con la placa padre
2026-06-22 Ordene los gate drivers
2026-06-23 Casi todo padre
2026-06-25 correcciones
2026-06-26 pcb terminada para evaluar
2026-06-26 PCB finalizado para evaluar
2026-06-28 Algunos cambios
2026-06-29 Corregi cosas de la placa
2026-06-30 Modificaciones varias
